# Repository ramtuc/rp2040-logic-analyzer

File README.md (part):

# RP2040 16ch ロジックアナライザ基板

RP2040 と TI の TXU0104（レベル変換 ×4）で作った、**16ch のロジックアナライザ基板**です。1.8V〜5V のロジックをそのまま受け、[sigrok-pico](https://github.com/pico-coder/sigrok-pico) のファームを書くと **PulseView（sigrok）から I2C・SPI・UART をデコード**できます。4 層・65 × 45mm で、部品実装は JLCPCB の PCBA に任せています。

| 項目 | 内容 |
|:---|:---|
| ch 数 | 16ch（GP0〜GP15） |
| 入力 | 1.8V〜5V のロジック（最大 5.5V）。TXU0104 のシュミット入力・内蔵プルダウン |
| しきい値の基準 | VREF をスライドスイッチ SW1 で選ぶ（3.3V／EXT／5V） |
| ファーム | sigrok-pico `pico_dig26.uf2`（PulseView nightly の `raspberrypi-pico` ドライバ） |
| 基板 | 4 層（L1 信号／L2 GND／L3 電源／L4 信号）・65 × 45mm・1.6mm |
| 製造 | JLCPCB（PCB＋Economic PCBA） |

---

## 状態（2026-10-10）

- **A0 基板の検証は第3回（実戦投入）で一区切りです。** 第2回で立ち上げ（3.3V レール 3.303V・水晶 12MHz・RP2040 内蔵 LDO 1.096V・PulseView で I2C をデコード）、第3回でしきい値・サンプリング上限・時間窓を実測し、SPI／UART／サーボ PWM をデコードしました。第3回の実測値（A0・SW1 改修済み・`pico_dig26.uf2`）:
  - **1.8V ロジックは EXT で読めます。** VREF = 1.806V（EXT）で VT+ 1.399V／VT− 0.732V。雑音を抑えた入力で測り直した 3.3V 位置は VT+ 2.401V／VT− 1.395V、5V 位置は VT+ 3.290V／VT− 2.138V（0.05V 刻みの掃引）。VT+ は TXU0104 データシートの近い VCCA 行の上限より高めで、原因は未特定です
  - **サンプリングレートの上限は 120MS/s です。** PulseView の一覧には 150M〜240M も出ますが、選ぶと取り込みに失敗します。12MHz・24MHz の矩形波は 120／60MS/s で正しく読め、20MS/s では 12MHz が 8MHz に化けます（エイリアス）
  - **16ch・120MS/s で一度に取れるのは 10 万サンプル（約 0.84ms）までです。** それ以上を指定すると、エラーなしで約 0.45ms に打ち切られます
  - SPI（74HC595 への 1 バイト・shiftOut とハードウェア SPI 1MHz）、UART（115200／9600bps）、サーボ PWM（50Hz・パルス幅 0.5〜2.4ms）を PulseView のデコーダで読めました
- **次版 A1 の基板データを作りました（2026-10-10）。** SW1 の pad1／pad2 のネットを回路図に合わせて入れ替え（pad1 = 3.3V・pad2 = VREF）、VREF の配線を pad2 へ引き直したものです。DRC エラー 0・未配線 0、基板と回路図のネット照合は 88 ネットすべて一致。`hardware/jlcpcb/` の製造データは A1 に更新してあります。**A1 はまだ製造していません。** 手元で検証した基板は A0 を改修したものです

### 既知の問題（A0）：SW1 のコモンはピン 2（A1 で修正済み）

筆者が注文した A0 の基板にあった問題です。VREF 切替スイッチ SW1（SK13D07VG5・C393948）のコモンは**ピン 2**（孤立したピン 1 の隣）ですが、A0 の基板は pad1 をコモン（VREF）として配線していました。改修前の A0 では、

- 「5V」位置で LDO の 3.3V 出力と USB の 5V が直結します
- 「EXT」位置で J3 に 3.3V が出ます

A0 の基板は、改修を済ませるまで **SW1 を 1 番目の位置（3.3V）から動かさないでください**。

**A0 の基板を使う場合の改修方法（部品側）**: pad2（3.3V）は内層の電源プレーンに直結でパターンを切れないため、スイッチのピン 1 とピン 2 を基板の穴から切り離し、**スイッチのピン 2（コモン）→ pad1（VREF）、スイッチのピン 1 → pad2（3.3V）**をジャンパ線で交差させます。改修後の VREF は「3.3V」3.303V／「EXT」0V（J3 未接続）／「5V」4.895V でした。改修の手順と写真は[第2回の記事](https://electwork.net/posts/jlcpcb-rp2040-logic-analyzer-02-bringup-first-i2c-decode/)にあります。

回路図と自作シンボル（`lib/logicana.kicad_sym`）は 2026-10-04 に、**PCB と製造データは A1（2026-10-10）で訂正済み**です（[SPEC.md §17](SPEC.md)）。A1 は pad1 = 3.3V・pad2 = VREF（コモン）で、改修なしで「3.3V／EXT／5V」の 3 位置が正しく切り替わります。A1 の基板はまだ製造していません。

---

## 製造データ

| 置き場所 | 中身 | 扱い |
|:---|:---|:---|
| **[hardware/jlcpcb/](hardware/jlcpcb/)** | **A1** の製造データ（Gerber 16 ファイル・BOM・CPL）。`hardware/out/` の kicad-cli 出力をそのまま置いたもの | **発注に使う正規データ**。**A1 はまだ製造していません**（筆者はこのデータでの発注を行っていません） |
| [hardware/out/](hardware/out/) | KiCad（kicad-cli）から出力した現行（A1）の Gerber・ドリル・BOM（`bom-jlcpcb.csv`）・CPL（`cpl-jlcpcb.csv`）・DRC・照合表 | 設計側の出力。`uv run tools/make_outputs.py` で再生成 |
| [hardware/out/a1/](hardware/out/a1/) | A1 の出力一式のスナップショット（Gerber zip・BOM・CPL・DRC・照合表・レンダ）と、A0 → A1 の修正スクリプト `apply_sw1_fix.py`・検算スクリプト | 記録 |

- **A1 と A0 の違いは SW1 まわりだけ**です。SW1 の pad1／pad2 のネットの入れ替え（pad1 = 3.3V・pad2 = VREF）、VREF の配線（表面 0.5mm）を pad1 から pad2 へ引き直し、内層 L3 の 3.3V プレーンの再充填、表シルク「RP2040 LA A1」、裏シルクに「CERN-OHL-P v2」。部品・配置・ほかの配線・穴（数と径）・BOM・CPL は A0 と同じです
- A0 の発注では、**USB-C（J1）は注文時に部品が入手できなかったため、実装から外して手はんだ**にしました。BOM / CPL のファイルには J1（C165948）が入ったままで、注文画面の部品照合で実装から外しています。A1 の BOM / CPL は A0 と同一で、J1 も入ったままです（在庫があれば実装に含めて構いません）
- SW1 とピンヘッダ J2・J3 は THT 部品なので、設計段階から手はんだの予定です

---

## JLCPCB で発注する手順

A1 の基板は、`hardware/jlcpcb/` の製造データでそのまま発注できます。以下は A0 の注文（2026 年 9 月）で実際に選んだ項目で、A1 でも同じです（A1 のデータでの発注は、筆者はまだ行っていません）。JLCPCB の画面の項目名や並びは更新で変わることがあるので、見当たらないときは同じ意味の項目を探してください。発注の流れの一般的な説明は[第1回の記事](https://electwork.net/posts/jlcpcb-rp2040-logic-analyzer-01-design-and-order/)に、この基板での選び方は[第3回の記事](https://electwork.net/posts/jlcpcb-rp2040-logic-analyzer-03-field-test/)にもあります。

> [!NOTE]
> **`hardware/jlcpcb/` は A1（SW1 の配線を直したデータ）です。** A0 からの変更は SW1 まわり（2 パッドのネットと VREF の配線 1 本）だけで、A1 の基板はスイッチの改修なしで使えますが、**A1 の実機はまだありません**。

### 手順

1. **Gerber を zip にしてアップロード**: `hardware/jlcpcb/gerbers/` の 16 ファイルを 1 つの zip にまとめ（`hardware/out/rp2040-logic-analyzer-gerbers.zip` が同じ内容の zip です）、注文ページでアップロードします。層数 4・外形 65 × 45mm と読み取られれば、外形とドリルまで入っています
2. **基板の仕様を選ぶ**: 下の表の項目が設計の前提に関わります。それ以外（表面処理・レジスト色など）は好みで構いません（A0 は HASL・緑）

   | 項目 | 選ぶ値 | 理由 |
   |:---|:---|:---|
   | 層数 | 4（自動認識） | 4 層設計 |
   | 板厚 | 1.6mm | スタックアップの前提 |
   | スタックアップ（インピーダンス制御の層構成） | **JLC04161H-7628** | USB 差動ペアの線幅 0.30mm／間隔 0.15mm はこの層構成で計算しています |
   | 最小ビア（穴径／外径） | **0.3mm/(0.4/0.45mm)** | 設計のビアは穴 0.30mm・外径 0.45mm |
   | 枚数 | 5 | A0 と同じ。段取り費が固定なので 2 枚と 5 枚の差は小さいです |

3. **PCB Assembly を ON**: **Economic**・実装面 **Top**・枚数 **5**。SMD 部品はすべて表面なので、片面実装で足ります
4. **BOM と CPL をアップロード**: `hardware/jlcpcb/bom-jlcpcb.csv`（19 行・全行に JLCPCB 部品番号入り）と `hardware/jlcpcb/cpl-jlcpcb.csv`（SMD 68 部品の座標・回転・面）
5. **部品の照合**: 19 行がすべて JLCPCB の部品に当たり、在庫があるかを見ます
   - 区分は Basic 12 種・Extended 6 種（RP2040・TXU0104・USB-C・USBLC6・水晶 ABM8-272-T3・27Ω）。Economic PCBA では Extended 1 種類ごとに段取り費がかかります
   - **在庫切れの行は、実装から外して手はんだに回します。** A0 の注文では USB-C（J1・C165948）が在庫切れで、この方法にしました。在庫があれば、そのまま実装に含めて構いません
   - 汎用の抵抗・コンデンサが在庫切れなら、同じ値・同じサイズ（0402／0805）の Basic 品に差し替えます
   - SW1（C393948）は BOM にありますが CPL にはなく（THT・手はんだの予定）、JLCPCB 側では未実装扱いになります
6. **配置プレビューで向きを確認**: CPL の回転が合っているかは、ここで目で確かめます。見るところは RP2040（U1）の 1 番ピン、TXU0104（U3〜U6）、SOT-223 の LDO（U7）のタブ、USB-C（J1）、LED（D1〜D3）の極性です。ずれていれば、その画面で回転を直します（CPL の回転補正の記録は `hardware/out/cpl-rotation-report.md`）
7. **カートへ**: 配送方法を選んで注文します。A0 は DHL Express で、注文確定から 5 日で届きました

### 届いたら手はんだする部品

| 部品 | 種類 | 備考 |
|:---|:---|:---|
| J1 USB-C（TYPE-C-31-M-12・C165948） | SMD・0.5mm ピッチ | PCBA で在庫がなく外した場合だけ |
| SW1 スライドスイッチ（SK13D07VG5・C393948） | THT・ライトアングル | JLCPCB では実装されないので別に用意する。A1 の基板は改修不要。A0 の基板は取り付けと同時に上の改修をする |
| J2 2×16 ピンヘッダ（2.54mm） | THT | プローブ入力。BOM に含めていないので別に用意する |
| J3 1×3 ピンヘッダ（2.54mm） | THT | 外部 VREF（EXT）。同上 |

手はんだが終わったら、下の「ファーム」の手順で `pico_dig26.uf2` を書き込みます。

### 費用の目安

A0（5 枚・USB-C 実装なし）の実際の注文額は、製品代 $73.10（PCB＋Economic PCBA・1 枚あたり $14.62）＋送料 $17.04（DHL Express）＝ **$90.14**（2026 年 9 月）でした。部品の価格と在庫、Extended の種類数、配送方法で変わります。手はんだ用の SW1・ピンヘッダは別にかかります。

---

## ファーム

1. sigrok-pico の [release フォルダ](https://github.com/pico-coder/sigrok-pico/tree/main/pico_sdk_sigrok/release)から **`pico_dig26.uf2`** を取得する
2. BOOT ボタン（SW2）を押しながら USB を挿す（またはリセットする）と、PC に RPI-RP2 ドライブが現れる。フラッシュが空なら自動でこの状態になる
3. `pico_dig26.uf2` を RPI-RP2 ドライブにコピーする → COM ポート（VID 2E8A / PID 000A）が現れる

- **`pico_baseline.uf2` は書かないでください。** GP0 を UART の送信ピンとして出力にするため、CH0 の TXU0104 の出力とぶつかります（[SPEC.md §2.3](SPEC.md)）
- PulseView は**リリース版 0.4.2 では使えません**（`raspberrypi-pico` ドライバが未収録）。[sigrok Downloads](https://sigrok.org/wiki/Downloads) から nightly 版を入れ、Connect to Device でドライバ **RaspberryPI PICO (raspberrypi-pico)** と COM ポートを選んでスキャンします
- **PulseView のチャンネル名は D2 から始まります。** 基板の **CH n は PulseView の D(n+2)**（CH0 = D2、CH15 = D17）です（sigrok-pico release の README にある PulseView 側の仕様）

---

## 使い方（最小）

### VREF の選び方

TXU0104 の入力しきい値は、入力側電源 VREF（VCCA）に応じて変わります。**測る相手の電源電圧に VREF を合わせます。**

| 測る相手 | SW1 | 備考 |
|:---|:---|:---|
| 3.3V ロジック | 3.3V | 基板内の LDO 出力 |
| 5V ロジック | 5V | USB の VBUS |
| 1.8V などそれ以外 | EXT | J3 に相手の電源電圧を入れる。**VREF 3.3V のままでは 1.8V ロジックの High を安定して読めません** |

- **J3（外部 VREF）を外してから SW1 を切り替えてください。** SW1 は shorting 型で、切り替えの途中で外部電源と内蔵電源が一瞬つながります
- EXT 位置で J3 に何もつないでいないと、**全 ch が反応しません**（VREF = 0V で TXU0104 の出力が Hi-Z）。VREF の LED（D2）が消えていれば、この状態です

### プローブヘッダ J2

2×16 ピン（2.54mm）。**内側 1 列が CH0〜CH15、外側 1 列はすべて GND** です。1ch ごとに隣の GND を使えます。

### 注意

- プローブ入力と EXT は **0〜5.5V** まで。過電圧・負電圧の保護回路はありません（直列 100Ω のみ）
- しきい値付近の信号は、入力の雑音がヒステリシスを超えるとトグルします。配線を短くし、GND をしっかり取ってください

---

## ディレクトリ構成

```
README.md            この文書
SPEC.md              仕様書（ファーム選定・IC 選定・入力回路・ピン割り当て・BOM・実機チェックリスト・改版メモ）
KICAD-KIT.md         KiCad の作業メモ（ライブラリ・BOM/CPL の出し方・4 層の DRC とスタックアップ・回路図チェックリスト）
docs/images/         README 用の写真
hardware/            KiCad 10 プロジェクト
  rp2040-logic-analyzer.kicad_pro / .kicad_sch / .kicad_pcb
  sym-lib-table / fp-lib-table      logicana / lcsc の登録（${KIPRJMOD}/../lib/...）
  out/                              kicad-cli の出力（schematic.pdf・Gerber・BOM / CPL・DRC・照合表・review/）と、配線作業で使った補助スクリプト（*.py）
    a1/                             A1 の出力のスナップショットと A0 → A1 の修正スクリプト（apply_sw1_fix.py）・プレーンの検算（check_sw1_plane.py）
  jlcpcb/                           A1 の製造データ（Gerber・BOM・CPL・未製造）
tools/
  gen_schematic.py   回路図の生成スクリプト（Python 3.12・標準ライブラリのみ）
  verify_netlist.py  kicad-cli のネットリストを期待表と照合
  verify_pcb_netlist.py
                     基板の全パッドのネットを回路図のネットリストと照合（→ hardware/out/pcb-netlist-check.md）
  check_kit5.py      回路図チェックリストをネットリストから機械検査
  gen_pcb.py         配置済み・未配線の基板を生成（配線は freerouting と手作業）
  fanout_planes.py / route_pcb.py / finish_pcb.py
                     GND・3V3 のファンアウト／freerouting の自動配線／ベタとビアスティッチの仕上げ（KiCad 同梱の python で実行）
  make_outputs.py    配線済み基板から製造データ（Gerber zip・BOM・CPL・DRC）とレビュー用画像を出力
  uno-r4-clock/      Arduino UNO R4 WiFi の GPT で 12／16／24／1MHz の矩形波を D6 に出すスケッチ（サンプリング上限テストの信号源。README あり）
  uno-r4-spi-uart/   UNO R4 WiFi から 74HC595 へ SPI（shiftOut／ハードウェア SPI 1MHz）を送り、同時に Serial1 から UART を出すスケッチ（第3回の SPI／UART 測定用）
  uno-r4-servo/      UNO R4 WiFi の D9 からサーボ PWM（0°→90°→180° を 2 秒ごと）を出すスケッチ（第3回のサーボ測定用）
lib/
  logicana.kicad_sym 自作シンボル 4 個（TXU0104PWR / SW_SP3T_SK13D07VG5 / SW_Push_TS1187A / VREF）
  lcsc/              LCSC 由来のライブラリ（リポジトリに含めない・下記で各自生成）
```

回路図は [hardware/out/schematic.pdf](hardware/out/schematic.pdf)（A3・1 ページ）で見られます。

---

## 回路図の再現手順

回路図は手描きではなく `tools/gen_schematic.py` の出力です。部品の位置・結線・ネット名はすべてスクリプトに書いてあり、再実行すると同じファイルになります（UUID は固定名前空間の uuid5）。前提は `uv`（cpython 3.12）と KiCad 10（`kicad-cli`）。

```
uv run tools/gen_schematic.py                # hardware/ に .kicad_sch / .kicad_pro / sym-lib-table / fp-lib-table を出力
uv run tools/gen_schematic.py --check        # 既存出力と一致するか（冪等性の確認）
uv run tools/gen_schematic.py --selftest     # 回転ごとのピン位置を kicad-cli のネットリストで実測
kicad-cli sch erc --severity-all --format report -o hardware/out/erc.rpt hardware/rp2040-logic-analyzer.kicad_sch
uv run tools/verify_netlist.py               # → hardware/out/netlist-check.md
uv run tools/check_kit5.py                   # → hardware/out/kit5-check.md
uv run tools/verify_pcb_netlist.py           # → hardware/out/pcb-netlist-check.md（基板の全パッド ↔ 回路図のネット）
kicad-cli sch export pdf -o hardware/out/schematic.pdf hardware/rp2040-logic-analyzer.kicad_sch
uv run tools/make_outputs.py                 # → hardware/out/（DRC・Gerber zip・BOM・CPL・照合表・レンダ）
```

KiCad 標準ライブラリと `lib/logicana.kicad_sym` からシンボルを読み、`extends` を平坦化して `lib_symbols` に埋め込みます。結線はピン端のスタブ＋ローカルラベル、電源レールは電源シンボルです。ネットが変わる変更はスクリプト側に入れて再生成します。

### LCSC 由来のライブラリ（clone した人がやること）

`lib/lcsc/` はリポジトリに含めていません（LCSC / EasyEDA 由来で、再配布できるライセンスか確認できなかったため）。次のコマンドで各自の環境に生成し、KiCad 10 の形式に上げます。

```
py -m pip install --user easyeda2kicad
py -m easyeda2kicad --full --project-relative --lcsc_id C318884 --output <repo>/lib/lcsc/lcsc --overwrite
py -m easyeda2kicad --full --project-relative --lcsc_id C393948 --output <repo>/lib/lcsc/lcsc --overwrite
py -m easyeda2kicad --full --project-relative --lcsc_id C2286   --output <repo>/lib/lcsc/lcsc --overwrite
py -m easyeda2kicad --full --project-relative --lcsc_id C165948 --output <repo>/lib/lcsc/lcsc --overwrite
kicad-cli fp  upgrade <repo>/lib/lcsc/lcsc.pretty
kicad-cli sym upgrade <repo>/lib/lcsc/lcsc.kicad_sym
```

| LCSC | 部品 | 用途 |
|:---|:---|:---|
| C318884 | タクトスイッチ | SW2 / SW3 のフットプリント（必須） |
| C393948 | スライドスイッチ SK13D07VG5 | SW1 のフットプリント（必須） |
| C2286 | LED 赤 0603 | 照合用（任意・標準の `LED_SMD:LED_0603_1608Metric` を使う） |
| C165948 | USB-C 16P | 照合用（任意・標準の `Connector_USB:USB_C_Receptacle_HRO_TYPE-C-31-M-12` を使う） |

---

## 記事（electwork.net）

- 第1回 設計と発注: https://electwork.net/posts/jlcpcb-rp2040-logic-analyzer-01-design-and-order/
- 第2回 立ち上げ: https://electwork.net/posts/jlcpcb-rp2040-logic-analyzer-02-bringup-first-i2c-decode/
- 第3回 実戦投入（しきい値・サンプリング上限・時間窓の実測、SPI／UART／サーボのデコード、発注の手順）: https://electwork.net/posts/jlcpcb-rp2040-logic-analyzer-03-field-test/

---

## 提供

この基板の製造と部品実装は、JLCPCB の提供を受けています（PR）。JLCPCB: https://jlcpcb.com/jp?from=RamTuckeyPCB

---

## ライセンス

| 対象 | ライセンス |
|:---|:---|
| **ハードウェア設計データ** — `hardware/`（KiCad プロジェクト・製造データ・`out/` の出力）・`lib/logicana.kicad_sym`・`SPEC.md`・`KICAD-KIT.md` | **CERN-OHL-P-2.0**（[LICENSE](LICENSE)）。寛容型（permissive）で、改変版や製品に同じライセンスでの公開義務はありません |
| **ソフトウェア** — `tools/` の Python スクリプトと Arduino スケッチ、`hardware/out/` の Python スクリプト | **MIT**（[LICENSE-MIT](LICENSE-MIT)） |
| 記事（electwork.net）の文章・画像、`docs/images/` の写真 | 上記の対象外（All rights reserved） |

SPDX 識別子: ハードウェア `CERN-OHL-P-2.0`／ソフトウェア `MIT`。

ハードウェア設計データの表示（CERN-OHL-P-2.0 の Notice）:

> Copyright 2026 ramtuc (electwork.net).
> This source describes Open Hardware and is licensed under the CERN-OHL-P v2.
> You may redistribute and modify this documentation and make products using it under the terms of the CERN-OHL-P v2 (https://ohwr.org/cern_ohl_p_v2.txt). This documentation is distributed WITHOUT ANY EXPRESS OR IMPLIED WARRANTY, INCLUDING OF MERCHANTABILITY, SATISFACTORY QUALITY AND FITNESS FOR A PARTICULAR PURPOSE. Please see the CERN-OHL-P v2 for applicable conditions.
> Source Location: https://github.com/ramtuc/rp2040-logic-analyzer

### 第三者のもの

| 対象 | ライセンス・扱い |
|:---|:---|
| ファーム（sigrok-pico） | GPL-3.0。別のプロジェクトで、このリポジトリには含めていません |
| LCSC / EasyEDA 由来のライブラリ（`lib/lcsc/` など） | 同梱しません（`.gitignore` で除外。上の手順で各自生成） |
| KiCad 標準ライブラリ | 同梱しません |
| [gusmanb/logicanalyzer](https://github.com/gusmanb/logicanalyzer)（GPL-3.0） | 回路図・レイアウトは流用していません。TXU0104 採用という部品選定の事実のみ参考にしました |

---

## English summary

A 16-channel logic analyzer board based on the Raspberry Pi RP2040 and four TI TXU0104 level translators. It accepts 1.8 V to 5 V logic (max 5.5 V) with a selectable reference voltage (VREF: 3.3 V / external / 5 V via slide switch SW1), and works with PulseView (sigrok) through the [sigrok-pico](https://github.com/pico-coder/sigrok-pico) firmware `pico_dig26.uf2` (requires a PulseView nightly build; channel CH n appears as D(n+2) in PulseView). 4-layer, 65 x 45 mm, assembled by JLCPCB PCBA.

- **Status (2026-10-10):** Rev A0 is verified through Part 3 of the article series. Measured on A0 (SW1 reworked, `pico_dig26.uf2`): 1.8 V logic is readable with VREF = EXT (VT+ 1.399 V / VT− 0.732 V at VREF 1.806 V); with a low-noise input the 3.3 V position reads VT+ 2.401 V / VT− 1.395 V and the 5 V position VT+ 3.290 V / VT− 2.138 V (VT+ came out above the upper limit of the nearest TXU0104 datasheet row; cause not identified). The usable sample-rate ceiling is 120 MS/s (150 MS/s and above fail to capture); 12 MHz and 24 MHz square waves are read correctly at 120 and 60 MS/s, and 12 MHz aliases to 8 MHz at 20 MS/s. With 16 channels at 120 MS/s a single capture holds up to 100k samples (about 0.84 ms); larger settings are silently cut to about 0.45 ms. SPI (74HC595), UART (115200 / 9600 bps) and servo PWM (50 Hz, 0.5–2.4 ms) were decoded in PulseView. **Rev A1 board data (2026-10-10)** fixes the SW1 pad assignment (pad1 = 3.3 V, pad2 = VREF/common, VREF trace re-routed to pad2) with DRC 0 errors / 0 unconnected and a full PCB-vs-schematic net match (88/88 nets). **A1 has not been manufactured yet.**
- **Known issue (A0):** The common pin of SW1 (SK13D07VG5) is pin 2, not pin 1. The A0 PCB routes it incorrectly; A0 boards need a jumper rework on the switch side (switch pin 2 → pad1/VREF, switch pin 1 → pad2/3.3V). The schematic and symbol were corrected on 2026-10-04 and the PCB in Rev A1 (2026-10-10); A1 boards need no rework. **On an A0 board, until the rework is done, keep SW1 in position 1 (3.3 V): position 3 (5 V) shorts the 3.3 V LDO output to USB 5 V, and position 2 (EXT) puts 3.3 V on J3.**
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
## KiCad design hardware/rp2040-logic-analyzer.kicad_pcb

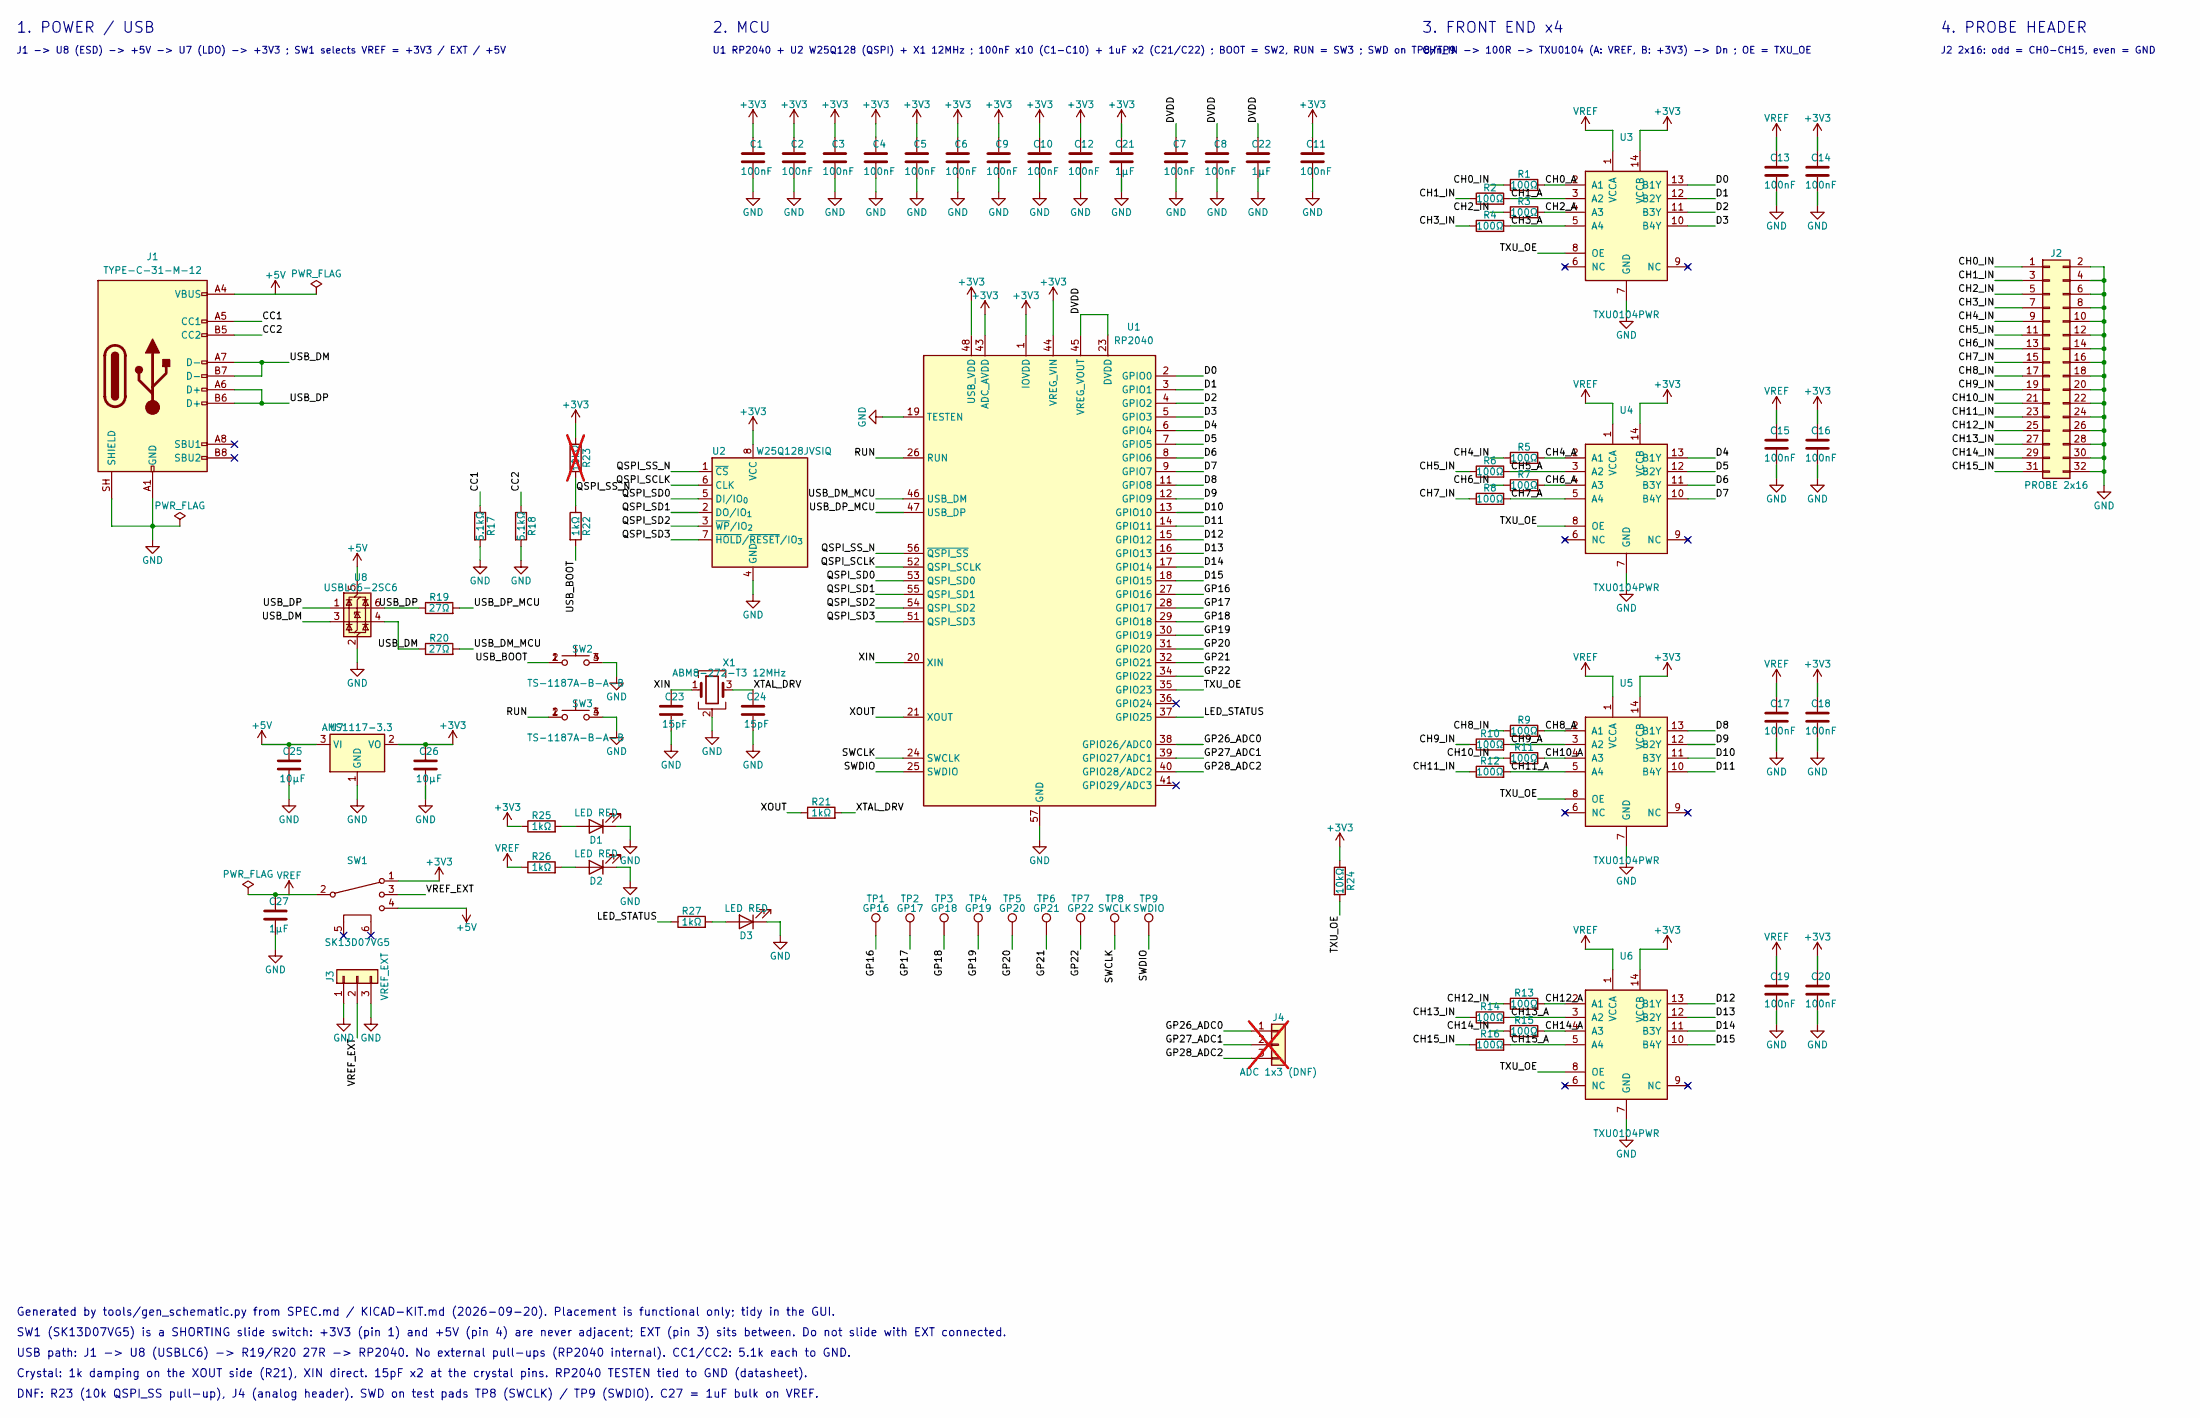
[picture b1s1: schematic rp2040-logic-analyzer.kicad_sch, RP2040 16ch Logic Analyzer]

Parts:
C1, C2, C3, C4, C5, C6, C7, C8, C9, C10, C11, C12, C13, C14, C15, C16, C17, C18, C19, C20: 100nF; C_0402_1005Metric
C21, C22, C27: 1µF; C_0402_1005Metric
C23, C24: 15pF; C_0402_1005Metric
C25, C26: 10µF; C_0805_2012Metric
D1, D2, D3: LED RED; LED_0603_1608Metric; LCSC Part # C2286
J1: TYPE-C-31-M-12; USB_C_Receptacle_HRO_TYPE-C-31-M-12; LCSC Part # C165948
J2: PROBE 2x16; PinHeader_2x16_P2.54mm_Vertical
J3: VREF_EXT; PinHeader_1x03_P2.54mm_Vertical
J4: ADC 1x3 (DNF); PinHeader_1x03_P2.54mm_Vertical; not fitted
R1, R2, R3, R4, R5, R6, R7, R8, R9, R10, R11, R12, R13, R14, R15, R16: 100Ω; R_0402_1005Metric
R17, R18: 5.1kΩ; R_0402_1005Metric
R19, R20: 27Ω; R_0402_1005Metric
R21, R22, R25, R26, R27: 1kΩ; R_0402_1005Metric
R23: 10kΩ; R_0402_1005Metric; not fitted
R24: 10kΩ; R_0402_1005Metric
SW1: SK13D07VG5; SW-TH_SK13D07VG5; LCSC Part # C393948
SW2, SW3: TS-1187A-B-A-B; SW-SMD_4P-L5.1-W5.1-P3.70-LS6.5-TL_H1.5; LCSC Part # C318884
TP1: GP16; TestPoint_Pad_1.0x1.0mm
TP2: GP17; TestPoint_Pad_1.0x1.0mm
TP3: GP18; TestPoint_Pad_1.0x1.0mm
TP4: GP19; TestPoint_Pad_1.0x1.0mm
TP5: GP20; TestPoint_Pad_1.0x1.0mm
TP6: GP21; TestPoint_Pad_1.0x1.0mm
TP7: GP22; TestPoint_Pad_1.0x1.0mm
TP8: SWCLK; TestPoint_Pad_1.0x1.0mm
TP9: SWDIO; TestPoint_Pad_1.0x1.0mm
U1: RP2040; QFN-56-1EP_7x7mm_P0.4mm_EP3.2x3.2mm; LCSC Part # C2040
U2: W25Q128JVSIQ; SOIC-8_5.3x5.3mm_P1.27mm; LCSC Part # C97521
U3, U4, U5, U6: TXU0104PWR; TSSOP-14_4.4x5mm_P0.65mm; LCSC Part # C2938871
U7: AMS1117-3.3; SOT-223-3_TabPin2; LCSC Part # C6186
U8: USBLC6-2SC6; SOT-23-6; LCSC Part # C7519
X1: ABM8-272-T3 12MHz; Crystal_SMD_3225-4Pin_3.2x2.5mm; LCSC Part # C20625731

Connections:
+3V3: C1.1, C2.1, C3.1, C4.1, C5.1, C6.1, C9.1, C10.1, C11.1, C12.1, C14.1, C16.1, C18.1, C20.1, C21.1, C26.1, R23.1, R24.1, R25.1, SW1.1, U1.1 (IOVDD), U1.10 (IOVDD), U1.22 (IOVDD), U1.33 (IOVDD), U1.42 (IOVDD), U1.43 (ADC_AVDD), U1.44 (VREG_VIN), U1.48 (USB_VDD), U1.49 (IOVDD), U2.8 (VCC), U3.14 (VCCB), U4.14 (VCCB), U5.14 (VCCB), U6.14 (VCCB), U7.2 (VO)
+5V: C25.1, J1.A4 (VBUS), J1.A9 (VBUS), J1.B4 (VBUS), J1.B9 (VBUS), SW1.4, U7.3 (VI), U8.5 (VBUS)
/CC1: J1.A5 (CC1), R17.1
/CC2: J1.B5 (CC2), R18.1
/CH0_A: R1.2, U3.2 (A1)
/CH0_IN: J2.1, R1.1
/CH1_A: R2.2, U3.3 (A2)
/CH1_IN: J2.3, R2.1
/CH2_A: R3.2, U3.4 (A3)
/CH2_IN: J2.5, R3.1
/CH3_A: R4.2, U3.5 (A4)
/CH3_IN: J2.7, R4.1
/CH4_A: R5.2, U4.2 (A1)
/CH4_IN: J2.9, R5.1
/CH5_A: R6.2, U4.3 (A2)
/CH5_IN: J2.11, R6.1
/CH6_A: R7.2, U4.4 (A3)
/CH6_IN: J2.13, R7.1
/CH7_A: R8.2, U4.5 (A4)
/CH7_IN: J2.15, R8.1
/CH8_A: R9.2, U5.2 (A1)
/CH8_IN: J2.17, R9.1
/CH9_A: R10.2, U5.3 (A2)
/CH9_IN: J2.19, R10.1
/CH10_A: R11.2, U5.4 (A3)
/CH10_IN: J2.21, R11.1
/CH11_A: R12.2, U5.5 (A4)
/CH11_IN: J2.23, R12.1
/CH12_A: R13.2, U6.2 (A1)
/CH12_IN: J2.25, R13.1
/CH13_A: R14.2, U6.3 (A2)
/CH13_IN: J2.27, R14.1
/CH14_A: R15.2, U6.4 (A3)
/CH14_IN: J2.29, R15.1
/CH15_A: R16.2, U6.5 (A4)
/CH15_IN: J2.31, R16.1
/D0: U1.2 (GPIO0), U3.13 (B1Y)
/D1: U1.3 (GPIO1), U3.12 (B2Y)
/D2: U1.4 (GPIO2), U3.11 (B3Y)
/D3: U1.5 (GPIO3), U3.10 (B4Y)
/D4: U1.6 (GPIO4), U4.13 (B1Y)
/D5: U1.7 (GPIO5), U4.12 (B2Y)
/D6: U1.8 (GPIO6), U4.11 (B3Y)
/D7: U1.9 (GPIO7), U4.10 (B4Y)
/D8: U1.11 (GPIO8), U5.13 (B1Y)
/D9: U1.12 (GPIO9), U5.12 (B2Y)
/D10: U1.13 (GPIO10), U5.11 (B3Y)
/D11: U1.14 (GPIO11), U5.10 (B4Y)
/D12: U1.15 (GPIO12), U6.13 (B1Y)
/D13: U1.16 (GPIO13), U6.12 (B2Y)
/D14: U1.17 (GPIO14), U6.11 (B3Y)
/D15: U1.18 (GPIO15), U6.10 (B4Y)
/DVDD: C7.1, C8.1, C22.1, U1.23 (DVDD), U1.45 (VREG_VOUT), U1.50 (DVDD)
/GP16: TP1.1, U1.27 (GPIO16)
/GP17: TP2.1, U1.28 (GPIO17)
/GP18: TP3.1, U1.29 (GPIO18)
/GP19: TP4.1, U1.30 (GPIO19)
/GP20: TP5.1, U1.31 (GPIO20)
/GP21: TP6.1, U1.32 (GPIO21)
/GP22: TP7.1, U1.34 (GPIO22)
/GP26_ADC0: J4.1, U1.38 (GPIO26/ADC0)
/GP27_ADC1: J4.2, U1.39 (GPIO27/ADC1)
/GP28_ADC2: J4.3, U1.40 (GPIO28/ADC2)
/LED_STATUS: R27.1, U1.37 (GPIO25)
/QSPI_SCLK: U1.52 (QSPI_SCLK), U2.6 (CLK)
/QSPI_SD0: U1.53 (QSPI_SD0), U2.5 (DI/IO_{0})
/QSPI_SD1: U1.55 (QSPI_SD1), U2.2 (DO/IO_{1})
/QSPI_SD2: U1.54 (QSPI_SD2), U2.3 (~WP/IO_{2})
/QSPI_SD3: U1.51 (QSPI_SD3), U2.7 (~HOLD/~RESET/IO_{3})
/QSPI_SS_N: R22.1, R23.2, U1.56 (~QSPI_SS), U2.1 (~CS)
/RUN: SW3.1 (A), SW3.2 (B), U1.26 (RUN)
/SWCLK: TP8.1, U1.24 (SWCLK)
/SWDIO: TP9.1, U1.25 (SWDIO)
/TXU_OE: R24.2, U1.35 (GPIO23), U3.8 (OE), U4.8 (OE), U5.8 (OE), U6.8 (OE)
/USB_BOOT: R22.2, SW2.1 (A), SW2.2 (B)
/USB_DM: J1.A7 (D-), J1.B7 (D-), R20.1, U8.3 (I/O2), U8.4 (I/O2)
/USB_DM_MCU: R20.2, U1.46 (USB_DM)
/USB_DP: J1.A6 (D+), J1.B6 (D+), R19.1, U8.1 (I/O1), U8.6 (I/O1)
/USB_DP_MCU: R19.2, U1.47 (USB_DP)
/VREF_EXT: J3.2, SW1.3
/XIN: C23.1, U1.20 (XIN), X1.1
/XOUT: R21.1, U1.21 (XOUT)
/XTAL_DRV: C24.1, R21.2, X1.3
GND: C1.2, C2.2, C3.2, C4.2, C5.2, C6.2, C7.2, C8.2, C9.2, C10.2, C11.2, C12.2, C13.2, C14.2, C15.2, C16.2, C17.2, C18.2, C19.2, C20.2, C21.2, C22.2, C23.2, C24.2, C25.2, C26.2, C27.2, D1.1 (K), D2.1 (K), D3.1 (K), J1.A1 (GND), J1.A12 (GND), J1.B1 (GND), J1.B12 (GND), J1.SH (SHIELD), J2.2, J2.4, J2.6, J2.8, J2.10, J2.12, J2.14, J2.16, J2.18, J2.20, J2.22, J2.24, J2.26, J2.28, J2.30, J2.32, J3.1, J3.3, R17.2, R18.2, SW2.3 (C), SW2.4 (D), SW3.3 (C), SW3.4 (D), U1.19 (TESTEN), U1.57 (GND), U2.4 (GND), U3.7 (GND), U4.7 (GND), U5.7 (GND), U6.7 (GND), U7.1 (GND), U8.2 (GND), X1.2 (G), X1.4 (G)
unnamed: D1.2 (A), R25.2
unnamed: D2.2 (A), R26.2
unnamed: D3.2 (A), R27.2
VREF: C13.1, C15.1, C17.1, C19.1, C27.1, R26.1, SW1.2 (COM), U3.1 (VCCA), U4.1 (VCCA), U5.1 (VCCA), U6.1 (VCCA)

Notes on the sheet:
Generated by tools/gen_schematic.py from SPEC.md / KICAD-KIT.md (2026-09-20). Placement is functional only; tidy in the GUI.
J1 -> U8 (ESD) -> +5V -> U7 (LDO) -> +3V3 ; SW1 selects VREF = +3V3 / EXT / +5V
USB path: J1 -> U8 (USBLC6) -> R19/R20 27R -> RP2040. No external pull-ups (RP2040 internal). CC1/CC2: 5.1k each to GND.
SW1 (SK13D07VG5) is a SHORTING slide switch: +3V3 (pin 1) and +5V (pin 4) are never adjacent; EXT (pin 3) sits between. Do not slide with EXT connected.
4. PROBE HEADER
CHn_IN -> 100R -> TXU0104 (A: VREF, B: +3V3) -> Dn ; OE = TXU_OE
2. MCU
1. POWER / USB
J2 2x16: odd = CH0-CH15, even = GND
U1 RP2040 + U2 W25Q128 (QSPI) + X1 12MHz ; 100nF x10 (C1-C10) + 1uF x2 (C21/C22) ; BOOT = SW2, RUN = SW3 ; SWD on TP8/TP9
3. FRONT END x4
DNF: R23 (10k QSPI_SS pull-up), J4 (analog header). SWD on test pads TP8 (SWCLK) / TP9 (SWDIO). C27 = 1uF bulk on VREF.
Crystal: 1k damping on the XOUT side (R21), XIN direct. 15pF x2 at the crystal pins. RP2040 TESTEN tied to GND (datasheet).

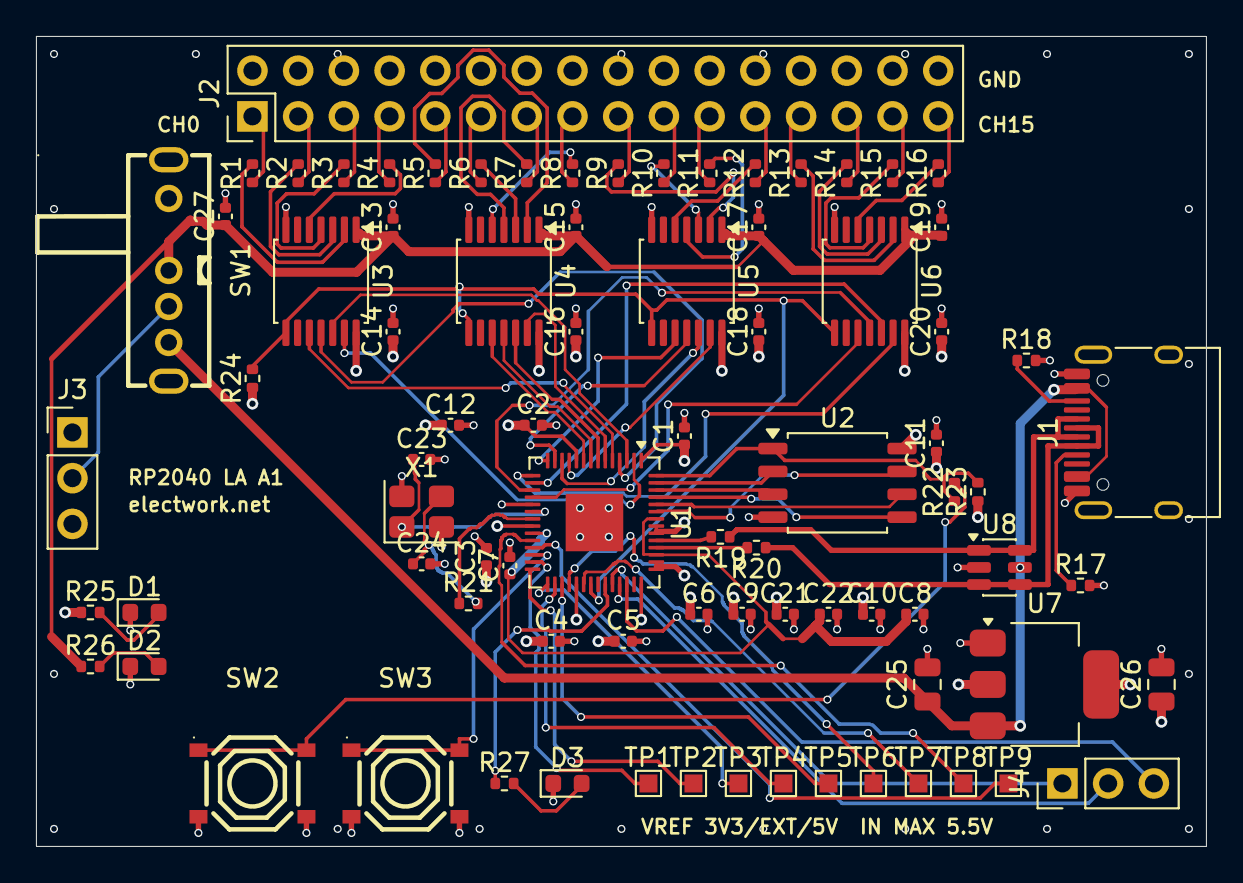
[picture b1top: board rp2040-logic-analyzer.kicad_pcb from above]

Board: 4 copper layers, 65.0 x 45.0 mm, 82 parts (0 on the bottom side), 88 nets.

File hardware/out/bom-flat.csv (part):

"Designator","Comment","Footprint","LCSC Part #","DNP","Description"
"C1","100nF","Capacitor_SMD:C_0402_1005Metric","","","100nF X7R 16V 0402, RP2040 IOVDD pin 1 (KIT §5-1)"
"C2","100nF","Capacitor_SMD:C_0402_1005Metric","","","100nF X7R 16V 0402, RP2040 IOVDD pin 10 (KIT §5-1)"
"C3","100nF","Capacitor_SMD:C_0402_1005Metric","","","100nF X7R 16V 0402, RP2040 IOVDD pin 22 (KIT §5-1)"
"C4","100nF","Capacitor_SMD:C_0402_1005Metric","","","100nF X7R 16V 0402, RP2040 IOVDD pin 33 (KIT §5-1)"
"C5","100nF","Capacitor_SMD:C_0402_1005Metric","","","100nF X7R 16V 0402, RP2040 IOVDD pin 42 (KIT §5-1)"
"C6","100nF","Capacitor_SMD:C_0402_1005Metric","","","100nF X7R 16V 0402, RP2040 IOVDD pin 49 (KIT §5-1)"
"C7","100nF","Capacitor_SMD:C_0402_1005Metric","","","100nF X7R 16V 0402, RP2040 DVDD pin 23 (KIT §5-1)"
"C8","100nF","Capacitor_SMD:C_0402_1005Metric","","","100nF X7R 16V 0402, RP2040 DVDD pin 50 (KIT §5-1)"
"C9","100nF","Capacitor_SMD:C_0402_1005Metric","","","100nF X7R 16V 0402, RP2040 USB_VDD pin 48 (KIT §5-1)"
"C10","100nF","Capacitor_SMD:C_0402_1005Metric","","","100nF X7R 16V 0402, RP2040 ADC_AVDD pin 43 (KIT §5-1)"
"C11","100nF","Capacitor_SMD:C_0402_1005Metric","","","100nF X7R 16V 0402, U2 flash VCC - place at U2 pin 8 (KIT §5-1)"
"C12","100nF","Capacitor_SMD:C_0402_1005Metric","","","100nF X7R 16V 0402, spare (SPEC §10 #22 予備)"
"C13","100nF","Capacitor_SMD:C_0402_1005Metric","","","100nF X7R 16V 0402, U3 VCCA (KIT §5-11)"
"C14","100nF","Capacitor_SMD:C_0402_1005Metric","","","100nF X7R 16V 0402, U3 VCCB (KIT §5-11)"
"C15","100nF","Capacitor_SMD:C_0402_1005Metric","","","100nF X7R 16V 0402, U4 VCCA (KIT §5-11)"
"C16","100nF","Capacitor_SMD:C_0402_1005Metric","","","100nF X7R 16V 0402, U4 VCCB (KIT §5-11)"
"C17","100nF","Capacitor_SMD:C_0402_1005Metric","","","100nF X7R 16V 0402, U5 VCCA (KIT §5-11)"
"C18","100nF","Capacitor_SMD:C_0402_1005Metric","","","100nF X7R 16V 0402, U5 VCCB (KIT §5-11)"
"C19","100nF","Capacitor_SMD:C_0402_1005Metric","","","100nF X7R 16V 0402, U6 VCCA (KIT §5-11)"
"C20","100nF","Capacitor_SMD:C_0402_1005Metric","","","100nF X7R 16V 0402, U6 VCCB (KIT §5-11)"
"C21","1µF","Capacitor_SMD:C_0402_1005Metric","","","1µF X5R 0402, RP2040 VREG_VIN pin 44 (KIT §5-2, 公式指定)"
"C22","1µF","Capacitor_SMD:C_0402_1005Metric","","","1µF X5R 0402, RP2040 VREG_VOUT pin 45 (KIT §5-2, 公式指定)"
"C23","15pF","Capacitor_SMD:C_0402_1005Metric","","","15pF NP0 0402 crystal load, XIN side (KIT §5-3)"
"C24","15pF","Capacitor_SMD:C_0402_1005Metric","","","15pF NP0 0402 crystal load, XOUT/XTAL_DRV side (KIT §5-3)"
"C25","10µF","Capacitor_SMD:C_0805_2012Metric","","","10µF X5R 16V 0805 LDO input (SPEC §10 #26)"
"C26","10µF","Capacitor_SMD:C_0805_2012Metric","","","10µF X5R 16V 0805 LDO output (SPEC §10 #26)"
"C27","1µF","Capacitor_SMD:C_0402_1005Metric","","","1µF X5R 0402, VREF bulk next to SW1 common (SPEC §5.4, Manager 2026-09-20)"
"D1","LED RED","LED_SMD:LED_0603_1608Metric","C2286","","LED red 0603, +3V3 power indicator (SPEC §6 D1)"
"D2","LED RED","LED_SMD:LED_0603_1608Metric","C2286","","LED red 0603, VREF indicator: dark when SW1 is not set (SPEC §6 D2)"
"D3","LED RED","LED_SMD:LED_0603_1608Metric","C2286","","LED red 0603, status on GP25 (SPEC §6 D3)"
"J1","TYPE-C-31-M-12","Connector_USB:USB_C_Receptacle_HRO_TYPE-C-31-M-12","C165948","","USB-C receptacle 16P, USB 2.0 (SPEC §10 #7, HRO TYPE-C-31-M-12)"
"J2","PROBE 2x16","Connector_PinHeader_2.54mm:PinHeader_2x16_P2.54mm_Vertical","","","Pin header 2x16 2.54mm probe header: odd row = CH0..CH15, even row = GND (SPEC §6 J2)"
"J3","VREF_EXT","Connector_PinHeader_2.54mm:PinHeader_1x03_P2.54mm_Vertical","","","Pin header 1x3 2.54mm, VREF EXT input (SPEC §6: EXT + GND x2). Pin 2 = EXT, pins 1/3 = GND"
"J4","ADC 1x3 (DNF)","Connector_PinHeader_2.54mm:PinHeader_1x03_P2.54mm_Vertical","","未実装(DNP)","Pin header 1x3 2.54mm, GP26/27/28 analog, DNF (SPEC §6 J4)"
"R1","100Ω","Resistor_SMD:R_0402_1005Metric","","","100Ω 1% 0402 input series CH0 (SPEC §5.3 / KIT §5-13)"
"R2","100Ω","Resistor_SMD:R_0402_1005Metric","","","100Ω 1% 0402 input series CH1 (SPEC §5.3 / KIT §5-13)"
"R3","100Ω","Resistor_SMD:R_0402_1005Metric","","","100Ω 1% 0402 input series CH2 (SPEC §5.3 / KIT §5-13)"
"R4","100Ω","Resistor_SMD:R_0402_1005Metric","","","100Ω 1% 0402 input series CH3 (SPEC §5.3 / KIT §5-13)"
"R5","100Ω","Resistor_SMD:R_0402_1005Metric","","","100Ω 1% 0402 input series CH4 (SPEC §5.3 / KIT §5-13)"
"R6","100Ω","Resistor_SMD:R_0402_1005Metric","","","100Ω 1% 0402 input series CH5 (SPEC §5.3 / KIT §5-13)"
"R7","100Ω","Resistor_SMD:R_0402_1005Metric","","","100Ω 1% 0402 input series CH6 (SPEC §5.3 / KIT §5-13)"
"R8","100Ω","Resistor_SMD:R_0402_1005Metric","","","100Ω 1% 0402 input series CH7 (SPEC §5.3 / KIT §5-13)"
"R9","100Ω","Resistor_SMD:R_0402_1005Metric","","","100Ω 1% 0402 input series CH8 (SPEC §5.3 / KIT §5-13)"
"R10","100Ω","Resistor_SMD:R_0402_1005Metric","","","100Ω 1% 0402 input series CH9 (SPEC §5.3 / KIT §5-13)"
"R11","100Ω","Resistor_SMD:R_0402_1005Metric","","","100Ω 1% 0402 input series CH10 (SPEC §5.3 / KIT §5-13)"
"R12","100Ω","Resistor_SMD:R_0402_1005Metric","","","100Ω 1% 0402 input series CH11 (SPEC §5.3 / KIT §5-13)"
"R13","100Ω","Resistor_SMD:R_0402_1005Metric","","","100Ω 1% 0402 input series CH12 (SPEC §5.3 / KIT §5-13)"
"R14","100Ω","Resistor_SMD:R_0402_1005Metric","","","100Ω 1% 0402 input series CH13 (SPEC §5.3 / KIT §5-13)"
"R15","100Ω","Resistor_SMD:R_0402_1005Metric","","","100Ω 1% 0402 input series CH14 (SPEC §5.3 / KIT §5-13)"
"R16","100Ω","Resistor_SMD:R_0402_1005Metric","","","100Ω 1% 0402 input series CH15 (SPEC §5.3 / KIT §5-13)"
"R17","5.1kΩ","Resistor_SMD:R_0402_1005Metric","","","5.1kΩ 1% 0402 USB-C CC pull-down (SPEC §10 #15)"
"R18","5.1kΩ","Resistor_SMD:R_0402_1005Metric","","","5.1kΩ 1% 0402 USB-C CC pull-down (SPEC §10 #15)"
"R19","27Ω","Resistor_SMD:R_0402_1005Metric","","","27Ω 1% 0402 USB D+ series termination, place next to RP2040 (SPEC §10 #16)"
"R20","27Ω","Resistor_SMD:R_0402_1005Metric","","","27Ω 1% 0402 USB D- series termination, place next to RP2040 (SPEC §10 #16)"
"R21","1kΩ","Resistor_SMD:R_0402_1005Metric","","","1kΩ 0402 crystal damping, XOUT side (SPEC §4.3 / KIT §5-4)"
"R22","1kΩ","Resistor_SMD:R_0402_1005Metric","","","1kΩ 0402 BOOTSEL series (SPEC §4.2 / KIT §5-6)"
"R23","10kΩ","Resistor_SMD:R_0402_1005Metric","","未実装(DNP)","10kΩ 0402 QSPI_SS pull-up, DNF (SPEC §4.2 / KIT §5-5)"
"R24","10kΩ","Resistor_SMD:R_0402_1005Metric","","","10kΩ 0402 TXU0104 OE pull-up to +3V3 (SPEC §5.3 / KIT §5-10)"
"R25","1kΩ","Resistor_SMD:R_0402_1005Metric","","","1kΩ 0402 LED current limit (SPEC §10 #21)"
"R26","1kΩ","Resistor_SMD:R_0402_1005Metric","","","1kΩ 0402 LED current limit (SPEC §10 #21)"
"R27","1kΩ","Resistor_SMD:R_0402_1005Metric","","","1kΩ 0402 LED current limit (SPEC §10 #21)"
"SW1","SK13D07VG5","lcsc:SW-TH_SK13D07VG5","C393948","","SP3T slide switch, THT right-angle, SHORTING type. Contact order +3V3 / EXT / +5V so +3V3 and +5V never bridge (SPEC §5.4, KIT §1.2.3)"
"SW2","TS-1187A-B-A-B","lcsc:SW-SMD_4P-L5.1-W5.1-P3.70-LS6.5-TL_H1.5","C318884","","Tactile switch, BOOTSEL: pulls QSPI_SS low via R22 (SPEC §6 SW2)"
"SW3","TS-1187A-B-A-B","lcsc:SW-SMD_4P-L5.1-W5.1-P3.70-LS6.5-TL_H1.5","C318884","","Tactile switch, RESET: pulls RUN low, no external parts (SPEC §6 SW3, KIT §5 RUN)"
"TP1","GP16","TestPoint:TestPoint_Pad_1.0x1.0mm","","","Test pad 1.0mm, GP16 (SPEC §6 J5 test pads for dgatf UART/config)"
"TP2","GP17","TestPoint:TestPoint_Pad_1.0x1.0mm","","","Test pad 1.0mm, GP17 (SPEC §6 J5 test pads for dgatf UART/config)"
"TP3","GP18","TestPoint:TestPoint_Pad_1.0x1.0mm","","","Test pad 1.0mm, GP18 (SPEC §6 J5 test pads for dgatf UART/config)"
"TP4","GP19","TestPoint:TestPoint_Pad_1.0x1.0mm","","","Test pad 1.0mm, GP19 (SPEC §6 J5 test pads for dgatf UART/config)"
"TP5","GP20","TestPoint:TestPoint_Pad_1.0x1.0mm","","","Test pad 1.0mm, GP20 (SPEC §6 J5 test pads for dgatf UART/config)"
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
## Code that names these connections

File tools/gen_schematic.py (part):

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    a7, b7 = j1.pin("A7"), j1.pin("B7")
    sch.route(a7, add(a7, 4, 0), add(b7, 4, 0), b7)
    sch.wire(add(a7, 4, 0), add(a7, 8, 0))
    sch.label("USB_DM", add(a7, 8, 0), 0)
    a6, b6 = j1.pin("A6"), j1.pin("B6")
    sch.route(a6, add(a6, 4, 0), add(b6, 4, 0), b6)
    sch.wire(add(b6, 4, 0), add(b6, 8, 0))
    sch.label("USB_DP", add(b6, 8, 0), 0)
    # SBU は未使用
    sch.nc(j1.pin("A8"))
    sch.nc(j1.pin("B8"))
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    # --- U8 USBLC6-2SC6（J1 直近・順序 J1 → ESD → 27Ω → RP2040）
    u8 = sch.place("Power_Protection:USBLC6-2SC6", "U8", G(60, 96), 0, footprint=FP["SOT23-6"], lcsc="C7519",
                   description="USB 2.0 ESD protection, SOT-23-6 (SPEC §10 #5)")
    sch.pin_label(u8, "1", "USB_DP", 4)     # I/O1（J1 側）
    sch.pin_label(u8, "3", "USB_DM", 4)     # I/O2（J1 側）
    sch.pin_power(u8, "5", "+5V")
    sch.pin_power(u8, "2", "GND")
    # --- R19 / R20 27Ω 直列終端。U8 の流し出し側（pin 6 / 4）から直結 → RP2040 側は *_MCU（KIT §4.1）
    p6, p4 = u8.pin("6"), u8.pin("4")
    r19 = R(sch, "R19", add(p6, 8, 0), "27Ω", rot=90, desc="27Ω 1% 0402 USB D+ series termination, place next to RP2040 (SPEC §10 #16)")
    sch.wire(p6, r19.pin(1))
    sch.label("USB_DP", r19.pin(1), 180)          # U8 の 1/6 はシンボル上は別ピン。ラベルで同じネットにする
    sch.pin_label(r19, 2, "USB_DP_MCU")
    r20 = R(sch, "R20", add(p4, 8, 4), "27Ω", rot=90, desc="27Ω 1% 0402 USB D- series termination, place next to RP2040 (SPEC §10 #16)")
    sch.route(p4, add(p4, 2, 0), add(p4, 2, 4), r20.pin(1))
    sch.label("USB_DM", r20.pin(1), 180)
    sch.pin_label(r20, 2, "USB_DM_MCU")

    # --- U7 AMS1117-3.3 ＋ 10µF ×2
    u7 = sch.place("Regulator_Linear:AMS1117-3.3", "U7", G(60, 116), 0, footprint=FP["SOT223"], lcsc="C6186",
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    sch.wire(p2, add(p2, 6, 0))
    sch.power("+3V3", add(p2, 6, 0))
    sch.wire(p3, add(p3, 4, 0))
    sch.label("VREF_EXT", add(p3, 4, 0), 0)
    sch.wire(p4, add(p4, 10, 0))
    sch.power("+5V", add(p4, 10, 0), DOWN)
    sch.nc(sw1.pin(5))
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    # --- J3 VREF EXT 入力（1×3・中央 = EXT、両端 GND）。90° 回転でピンを下向きに
    j3 = sch.place("Connector_Generic:Conn_01x03", "J3", G(60, 150), 90, value="VREF_EXT", footprint=FP["H1x03"],
                   description="Pin header 1x3 2.54mm, VREF EXT input (SPEC §6: EXT + GND x2). Pin 2 = EXT, pins 1/3 = GND")
    sch.pin_label(j3, 2, "VREF_EXT", 5)
    sch.pin_power(j3, 1, "GND")
    sch.pin_power(j3, 3, "GND")

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
    u1 = sch.place("MCU_RaspberryPi:RP2040", "U1", G(160, 92), 0, footprint=FP["QFN56"], lcsc="C2040",
                   description="Raspberry Pi RP2040, QFN-56 7x7mm (SPEC §10 #1)")
    # 右側 GPIO（GPIO0..7 = pin 2..9、GPIO8..15 = pin 11..18）
    for i in range(16):
        sch.pin_label(u1, str(2 + i + (1 if i >= 8 else 0)), f"D{i}", 4)
    gp = {16: "27", 17: "28", 18: "29", 19: "30", 20: "31", 21: "32", 22: "34", 23: "35", 24: "36", 25: "37",
          26: "38", 27: "39", 28: "40", 29: "41"}
    for n in range(16, 23):
        sch.pin_label(u1, gp[n], f"GP{n}", 4)
    sch.pin_label(u1, gp[23], "TXU_OE", 4)
    sch.nc(u1.pin(gp[24]))
    sch.pin_label(u1, gp[25], "LED_STATUS", 4)
    sch.pin_label(u1, gp[26], "GP26_ADC0", 4)
    sch.pin_label(u1, gp[27], "GP27_ADC1", 4)
    sch.pin_label(u1, gp[28], "GP28_ADC2", 4)
    sch.nc(u1.pin(gp[29]))
    # 左側
    sch.pin_power(u1, "19", "GND", 3)                # TESTEN: データシート「Ground on user boards」
    sch.pin_label(u1, "26", "RUN", 4)
    sch.pin_label(u1, "46", "USB_DM_MCU", 4)
    sch.pin_label(u1, "47", "USB_DP_MCU", 4)
    sch.pin_label(u1, "56", "QSPI_SS_N", 4)
    sch.pin_label(u1, "52", "QSPI_SCLK", 4)
    sch.pin_label(u1, "53", "QSPI_SD0", 4)
    sch.pin_label(u1, "55", "QSPI_SD1", 4)
    sch.pin_label(u1, "54", "QSPI_SD2", 4)
    sch.pin_label(u1, "51", "QSPI_SD3", 4)
    sch.pin_label(u1, "20", "XIN", 4)
    sch.pin_label(u1, "21", "XOUT", 4)
    sch.pin_label(u1, "24", "SWCLK", 4)              # KIT §5-15: SWD を出す（TP8 / TP9・Manager 2026-09-20）
    sch.pin_label(u1, "25", "SWDIO", 4)
    # 上側 電源。IOVDD(1,10,22,33,42,49) と DVDD(23,50) はシンボル上で同一点に重なる
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    sch.pin_power(u1, "48", "+3V3", 5)               # USB_VDD
    sch.pin_power(u1, "1", "+3V3", 3)                # IOVDD ×6
    sch.pin_power(u1, "44", "+3V3", 5)               # VREG_VIN
    vout, dvdd = u1.pin("45"), u1.pin("23")
    sch.route(vout, add(vout, 0, -3), add(dvdd, 0, -3), dvdd)
    sch.label("DVDD", add(vout, 0, -3), 90)
    # 下側 GND（EP = 57）
    sch.pin_power(u1, "57", "GND")

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    cap_to_rails(sch, "C10", x, row, "100nF", "+3V3", "100nF X7R 16V 0402, RP2040 ADC_AVDD pin 43 (KIT §5-1)"); x += 6
    cap_to_rails(sch, "C12", x, row, "100nF", "+3V3", "100nF X7R 16V 0402, spare (SPEC §10 #22 予備)"); x += 6
    cap_to_rails(sch, "C21", x, row, "1µF", "+3V3", "1µF X5R 0402, RP2040 VREG_VIN pin 44 (KIT §5-2, 公式指定)"); x += 8
    cap_to_rails(sch, "C7", x, row, "100nF", "DVDD", "100nF X7R 16V 0402, RP2040 DVDD pin 23 (KIT §5-1)"); x += 6
    cap_to_rails(sch, "C8", x, row, "100nF", "DVDD", "100nF X7R 16V 0402, RP2040 DVDD pin 50 (KIT §5-1)"); x += 6
    cap_to_rails(sch, "C22", x, row, "1µF", "DVDD", "1µF X5R 0402, RP2040 VREG_VOUT pin 45 (KIT §5-2, 公式指定)"); x += 8
    cap_to_rails(sch, "C11", x, row, "100nF", "+3V3", "100nF X7R 16V 0402, U2 flash VCC - place at U2 pin 8 (KIT §5-1)")

    # --- U2 W25Q128JVSIQ（QSPI 直結）
    u2 = sch.place("Memory_Flash:W25Q128JVS", "U2", G(118, 82), 0, value="W25Q128JVSIQ", footprint=FP["SOIC8"], lcsc="C97521",
                   description="128Mbit QSPI flash, SOIC-8 208mil (SPEC §10 #2)")
    sch.pin_label(u2, "1", "QSPI_SS_N", 4)
    sch.pin_label(u2, "6", "QSPI_SCLK", 4)
    sch.pin_label(u2, "5", "QSPI_SD0", 4)     # DI / IO0
    sch.pin_label(u2, "2", "QSPI_SD1", 4)     # DO / IO1
    sch.pin_label(u2, "3", "QSPI_SD2", 4)     # WP / IO2
    sch.pin_label(u2, "7", "QSPI_SD3", 4)     # HOLD / IO3
    sch.pin_power(u2, "8", "+3V3")
    sch.pin_power(u2, "4", "GND")

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    r22 = R(sch, "R22", G(92, 84), "1kΩ", desc="1kΩ 0402 BOOTSEL series (SPEC §4.2 / KIT §5-6)")
    mid = add(r23.pin(2), 0, 2)
    sch.route(r23.pin(2), mid, r22.pin(1))
    sch.label("QSPI_SS_N", mid, 0)
    sch.pin_label(r22, 2, "USB_BOOT")
    for ref, y, net, desc in (("SW2", 104, "USB_BOOT", "Tactile switch, BOOTSEL: pulls QSPI_SS low via R22 (SPEC §6 SW2)"),
                              ("SW3", 112, "RUN", "Tactile switch, RESET: pulls RUN low, no external parts (SPEC §6 SW3, KIT §5 RUN)")):
        sw = sch.place("logicana:SW_Push_TS1187A", ref, G(92, y), 0, value="TS-1187A-B-A-B", footprint=FP["TACT"], lcsc="C318884", description=desc)
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                   description="Crystal 12MHz 3225 4-pin, CL 10pF, ESR <= 50Ω (SPEC §4.3, Raspberry Pi 公式推奨品)")
    p1, p3 = x1.pin(1), x1.pin(3)
    sch.wire(p1, add(p1, -3, 0))
    sch.label("XIN", add(p1, -3, 0), 180)
    sch.wire(p3, add(p3, 3, 0))
    sch.label("XTAL_DRV", add(p3, 3, 0), 0)
    sch.pin_power(x1, "2", "GND")
    c23 = C(sch, "C23", add(p1, -3, 3), "15pF", desc="15pF NP0 0402 crystal load, XIN side (KIT §5-3)")
    sch.pin_power(c23, 2, "GND")
    c24 = C(sch, "C24", add(p3, 3, 3), "15pF", desc="15pF NP0 0402 crystal load, XOUT/XTAL_DRV side (KIT §5-3)")
    sch.pin_power(c24, 2, "GND")
    r21 = R(sch, "R21", G(128, 126), "1kΩ", rot=90, desc="1kΩ 0402 crystal damping, XOUT side (SPEC §4.3 / KIT §5-4)")
    sch.pin_label(r21, 1, "XOUT")
    sch.pin_label(r21, 2, "XTAL_DRV")

    # --- ステータス LED（GP25）
    led_chain(sch, 104, 142, "LED_STATUS", "R27", "D3", "LED red 0603, status on GP25 (SPEC §6 D3)")
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    # --- TXU_OE プルアップ 10kΩ → +3V3（KIT §5-10: VREF ではない）
    r24 = R(sch, "R24", G(204, 136), "10kΩ", desc="10kΩ 0402 TXU0104 OE pull-up to +3V3 (SPEC §5.3 / KIT §5-10)")
    sch.pin_power(r24, 1, "+3V3")
    sch.pin_label(r24, 2, "TXU_OE")

    # --- テストパッド GP16〜GP22（SPEC §6 J5。TestPoint シンボルは TP 参照子）
    tps = [(f"TP{i + 1}", f"GP{n}", f"Test pad 1.0mm, GP{n} (SPEC §6 J5 test pads for dgatf UART/config)") for i, n in enumerate(range(16, 23))]
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    # --- J4 アナログ 3ch（DNF）
    j4 = sch.place("Connector_Generic:Conn_01x03", "J4", G(190, 152), 0, value="ADC 1x3 (DNF)", footprint=FP["H1x03"], dnp=True,
                   description="Pin header 1x3 2.54mm, GP26/27/28 analog, DNF (SPEC §6 J4)")
    sch.pin_label(j4, 1, "GP26_ADC0", 4)
    sch.pin_label(j4, 2, "GP27_ADC1", 4)
    sch.pin_label(j4, 3, "GP28_ADC2", 4)

    # ================================================================================
    # 領域 3: フロントエンド ×4（U3〜U6・100Ω ×16・100nF ×8）     （右）
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            sch.label(f"CH{n}_A", r.pin(2), 0)
            sch.pin_label(r, 1, f"CH{n}_IN")
            sch.pin_label(u, str(13 - ch), f"D{n}", 4)          # B1Y..B4Y = pin 13..10
        sch.pin_label(u, "8", "TXU_OE", 4)
        sch.nc(u.pin("6"))
        sch.nc(u.pin("9"))
        va, vb = u.pin("1"), u.pin("14")
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        "Generated by tools/gen_schematic.py from SPEC.md / KICAD-KIT.md (2026-09-20). Placement is functional only; tidy in the GUI.",
        "SW1 (SK13D07VG5) is a SHORTING slide switch: +3V3 (pin 1) and +5V (pin 4) are never adjacent; EXT (pin 3) sits between. Do not slide with EXT connected.",
        "USB path: J1 -> U8 (USBLC6) -> R19/R20 27R -> RP2040. No external pull-ups (RP2040 internal). CC1/CC2: 5.1k each to GND.",
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

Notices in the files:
README.md:
A1 differs from A0 only around SW1 (two pad nets, one VREF trace, the L3 3.3 V plane refill, silkscreen "A1" and a "CERN-OHL-P v2" mark on the back); parts, placement, holes, BOM and CPL are identical.
- **License:** Hardware design data (`hardware/`, `lib/logicana.kicad_sym`, `SPEC.md`, `KICAD-KIT.md`) is licensed under **CERN-OHL-P-2.0** ([LICENSE](LICENSE)).
hardware/rp2040-logic-analyzer.kicad_pcb:
Generated by tools/gen_pcb.py. CERN-OHL-P-2.0
hardware/rp2040-logic-analyzer.kicad_sch:
Generated by tools/gen_schematic.py from SPEC.md / KICAD-KIT.md. CERN-OHL-P-2.0
